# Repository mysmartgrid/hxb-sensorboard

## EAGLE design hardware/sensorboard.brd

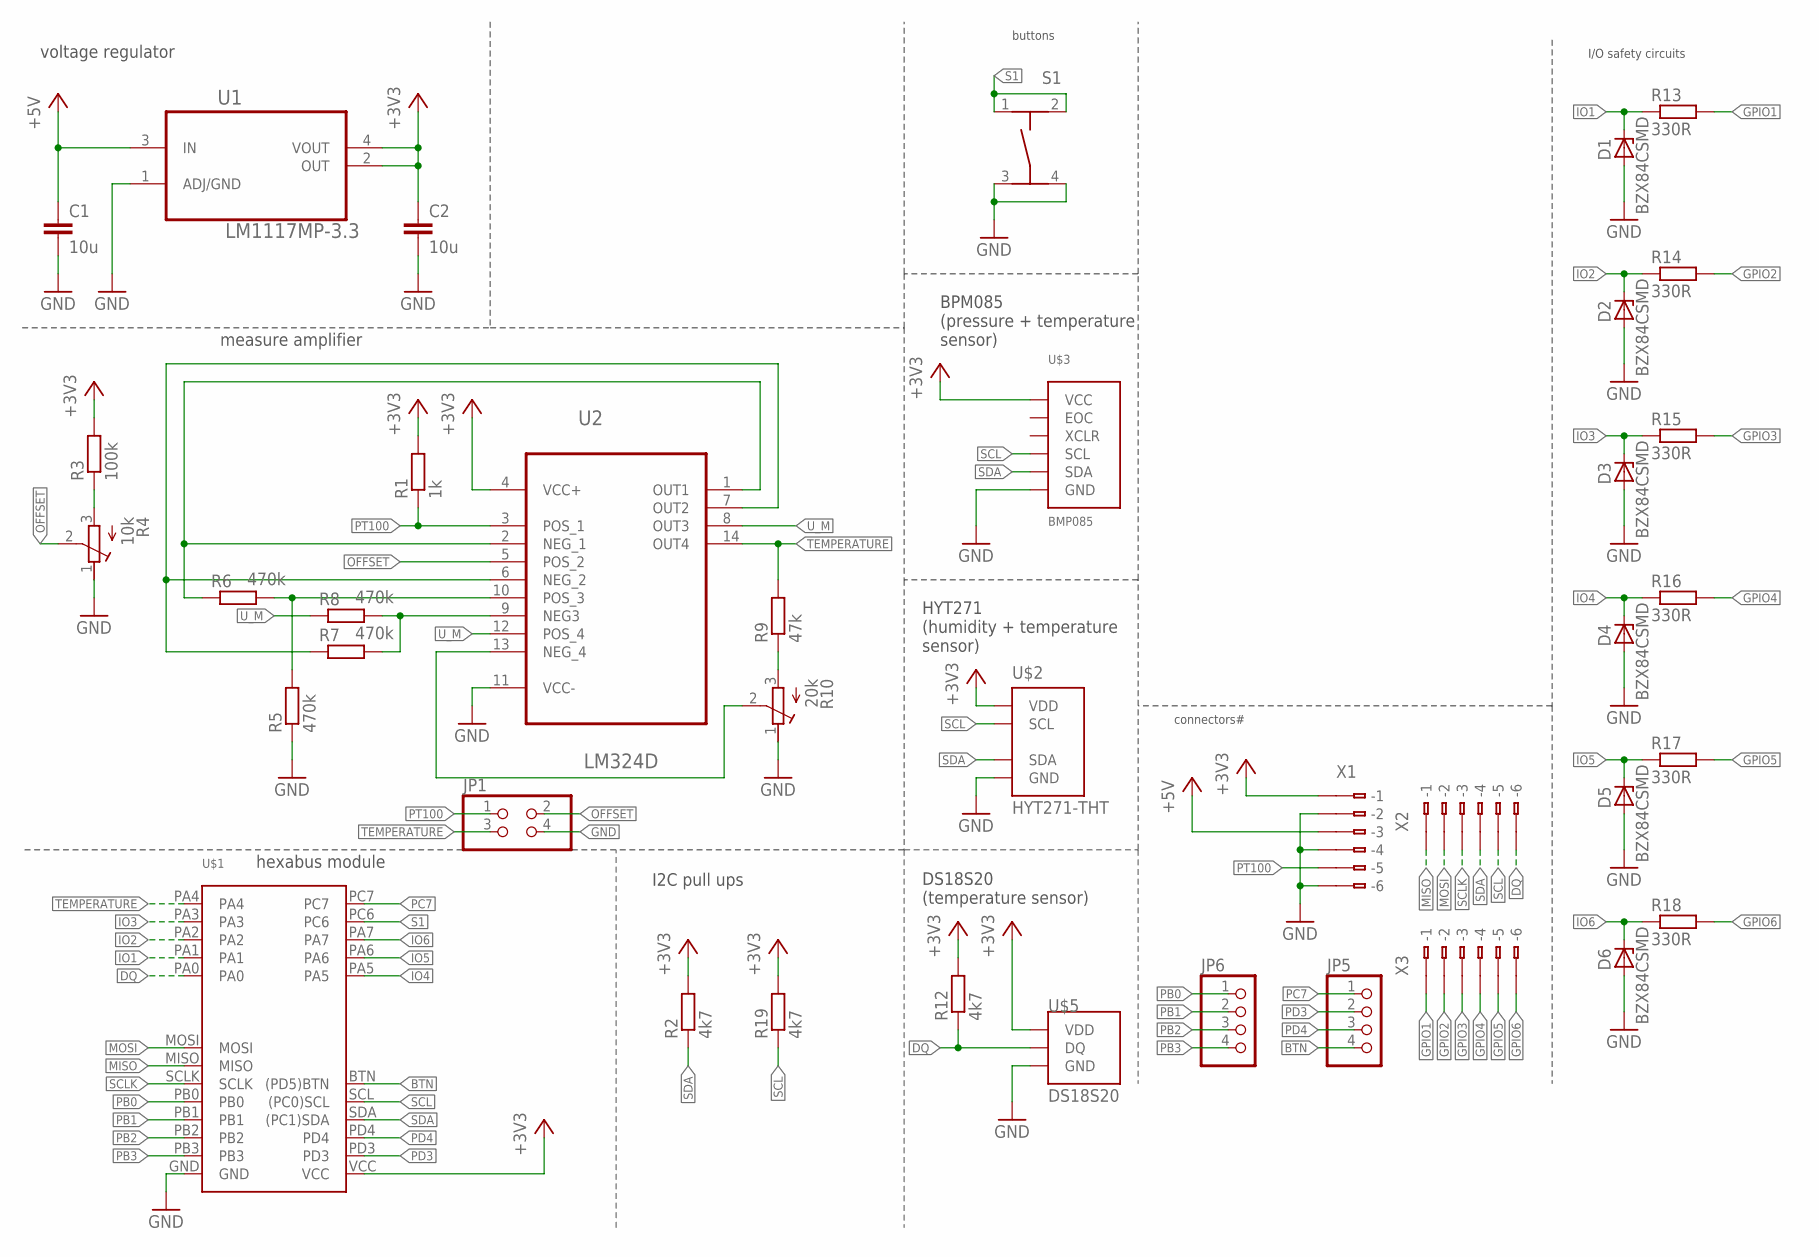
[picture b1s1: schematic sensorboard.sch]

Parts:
C1, C2: 10u; C0805
D1, D2, D3, D4, D5, D6: BZX84CSMD; TO236
JP1: PINHD-2X2; 2X02
JP5, JP6: PINHD-1X4; 1X04
R1: 1k; R0805
R2, R12, R19: 4k7; R0805
R3: 100k; R0805
R4: 10k; RTRIMT93YB
R5, R6, R7, R8: 470k; R0805
R9: 47k; R0805
R10: 20k; RTRIMT93YB
R13, R14, R15, R16, R17, R18: 330R; R0805
S1: TASTER-9314_SMD
U1: LM1117MP-3.3; SOT230P696X180-4N
U2: LM324D; SOIC127P600X175-14N
U$1: HEXABUS
U$2: HYT271-THT
U$3: BMP085; BREAKOUT
U$5: DS18S20; TO-92
X1, X2, X3: 233-206

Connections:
+3V3: C2.1, R1.2, R2.2, R3.2, R12.2, R19.2, U1.2 (OUT), U1.4 (VOUT), U2.4 (VCC+), U$1.VCC, U$2.VDD, U$3.VCC, U$5.VDD, X1.B1 (B-1)
+5V: C1.1, U1.3 (IN), X1.B3 (B-3)
BTN: JP5.4, U$1.BTN ((PD5)BTN)
DQ: R12.1, U$1.PA0, U$5.DQ, X2.B6 (B-6)
GND: C1.2, C2.2, D1.A, D2.A, D3.A, D4.A, D5.A, D6.A, JP1.4, R4.1 (E), R5.1, R10.1 (E), S1.3, S1.4, U1.1 (ADJ/GND), U2.11 (VCC-), U$1.GND, U$2.GND, U$3.GND, U$5.GND, X1.B2 (B-2), X1.B4 (B-4), X1.B6 (B-6)
GPIO1: R13.2, X3.B1 (B-1)
GPIO2: R14.2, X3.B2 (B-2)
GPIO3: R15.2, X3.B3 (B-3)
GPIO4: R16.2, X3.B4 (B-4)
GPIO5: R17.2, X3.B5 (B-5)
GPIO6: R18.2, X3.B6 (B-6)
IO1: D1.C, R13.1, U$1.PA1
IO2: D2.C, R14.1, U$1.PA2
IO3: D3.C, R15.1, U$1.PA3
IO4: D4.C, R16.1, U$1.PA5
IO5: D5.C, R17.1, U$1.PA6
IO6: D6.C, R18.1, U$1.PA7
MISO: U$1.MISO, X2.B1 (B-1)
MOSI: U$1.MOSI, X2.B2 (B-2)
unnamed: R6.1, U2.1 (OUT1), U2.2 (NEG_1)
unnamed: R7.1, U2.6 (NEG_2), U2.7 (OUT2)
unnamed: R5.2, R6.2, U2.10 (POS_3)
unnamed: R7.2, R8.2, U2.9 (NEG3)
unnamed: R10.2 (S), U2.13 (NEG_4)
unnamed: R9.1, R10.3 (A)
unnamed: R3.1, R4.3 (A)
OFFSET: JP1.2, R4.2 (S), U2.5 (POS_2)
PB0: JP6.1, U$1.PB0
PB1: JP6.2, U$1.PB1
PB2: JP6.3, U$1.PB2
PB3: JP6.4, U$1.PB3
PC7: JP5.1, U$1.PC7
PD3: JP5.2, U$1.PD3
PD4: JP5.3, U$1.PD4
PT100: JP1.1, R1.1, U2.3 (POS_1), X1.B5 (B-5)
S1: S1.1, S1.2, U$1.PC6
SCL: R19.1, U$1.SCL ((PC0)SCL), U$2.SCL, U$3.SCL, X2.B5 (B-5)
SCLK: U$1.SCLK, X2.B3 (B-3)
SDA: R2.1, U$1.SDA ((PC1)SDA), U$2.SDA, U$3.SDA, X2.B4 (B-4)
TEMPERATURE: JP1.3, R9.2, U2.14 (OUT4), U$1.PA4
U_M: R8.1, U2.8 (OUT3), U2.12 (POS_4)

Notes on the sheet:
hexabus module
voltage regulator
measure amplifier
HYT271 (humidity + temperature sensor)
DS18S20 (temperature sensor)
BPM085 (pressure + temperature sensor)
I/O safety circuits
buttons
connectors#
I2C pull ups

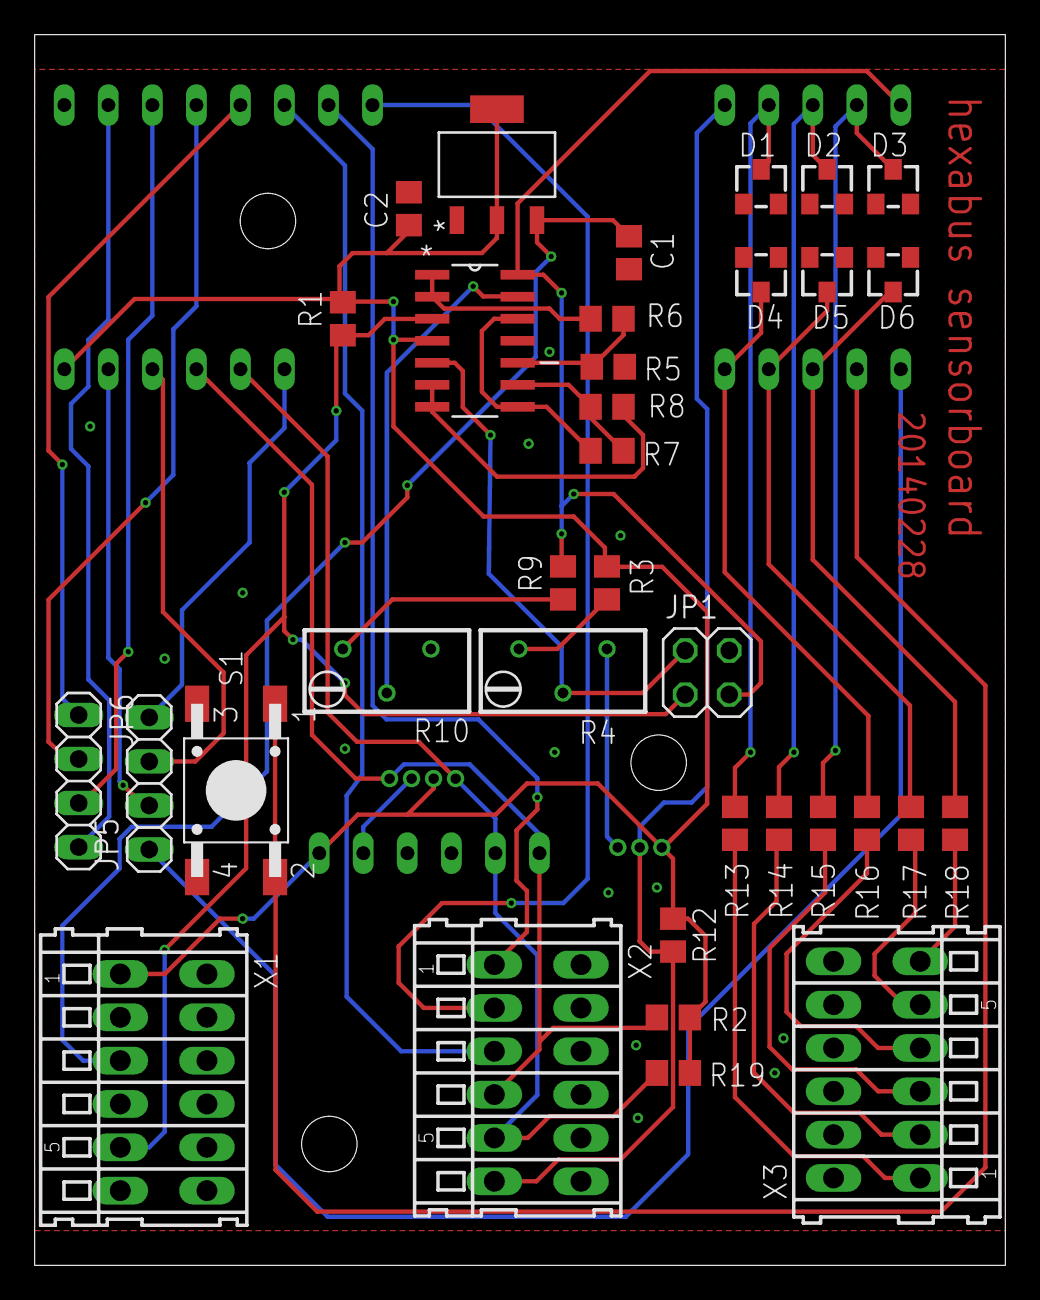
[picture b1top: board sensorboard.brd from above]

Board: 2 copper layers, 56.0 x 71.0 mm, 39 parts (0 on the bottom side), 41 nets.

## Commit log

2013-08-08 git files
2013-08-08 schematic with vreg, hxb, meas amp
2013-08-08 added pressure sensor
2013-08-08 added DS18S20
2013-08-12 added HYT271
2013-08-12 connector for SPI, I2C and onewire
2013-08-15 added GPIO safety cicuits
2013-08-15 added button
2013-08-15 added led driver. Unused pins to a pinheader
2013-08-15 first draft of brd
2013-08-23 preliminary placement
2013-08-23 changed HYT271 from SMD to THT
2013-08-29 routing
2013-08-29 organized placement print
2013-09-10 added version number
2013-10-18 changed repo structure
2014-02-19 added I2C pull up resistors
2014-02-19 optimized some routes
2014-02-25 added a pinheader for calibrating the measure amplifier. fixes #2
2014-02-28 removed bypass resistor. see #5
2014-02-28 updated version number
